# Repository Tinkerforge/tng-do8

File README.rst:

TNG DO8
=======

**This TNG module is currently in development.**

This repository contains the firmware source code and the hardware design
files. The documentation generator configs can be found at
https://github.com/Tinkerforge/generators

Repository Content
------------------

software/:
 * examples/: Examples for all supported languages
 * build/: Compiled files
 * src/: Source code of firmware
 * Makefile: Makefile to build project

hardware/:
 * Contains KiCad project files and additionally schematics as PDF

datasheets/:
 * Contains datasheets for sensors and complex ICs that are used

Hardware
--------

The hardware is designed with the open source EDA Suite KiCad
(http://www.kicad.org). Before you are able to open the files,
you have to install the Tinkerforge kicad-libraries
(https://github.com/Tinkerforge/kicad-libraries). You can either clone
them directly in hardware/ or clone them in a separate folder and
symlink them into hardware/
(ln -s kicad_path/kicad-libraries project_path/hardware). After that you
can open the .pro file in hardware/ with KiCad and from there view and
modify the schematics and the PCB layout.

Software
--------

If you want to do your own Brick/Bricklet firmware development we highly
recommend that you use our build environment setup script and read the
tutorial (https://www.tinkerforge.com/en/doc/Tutorials/Tutorial_Build_Environment/Tutorial.html).

To compile the C code we recommend you to install the newest GNU Arm Embedded
Toolchain (https://launchpad.net/gcc-arm-embedded/+download).
You also need to install bricklib2 (https://github.com/Tinkerforge/bricklib2).

You can either clone it directly in software/src/ or clone it in a
separate folder and symlink it into software/src/
(ln -s bricklib_path/bricklib2 project_path/software/src/). Finally make sure to
have CMake installed (http://www.cmake.org/cmake/resources/software.html).

After that you can build the firmware by invoking make in software/.
The firmware (.zbin) can then be found in software/build/ and uploaded
with brickv (click button "Flashing" on start screen).

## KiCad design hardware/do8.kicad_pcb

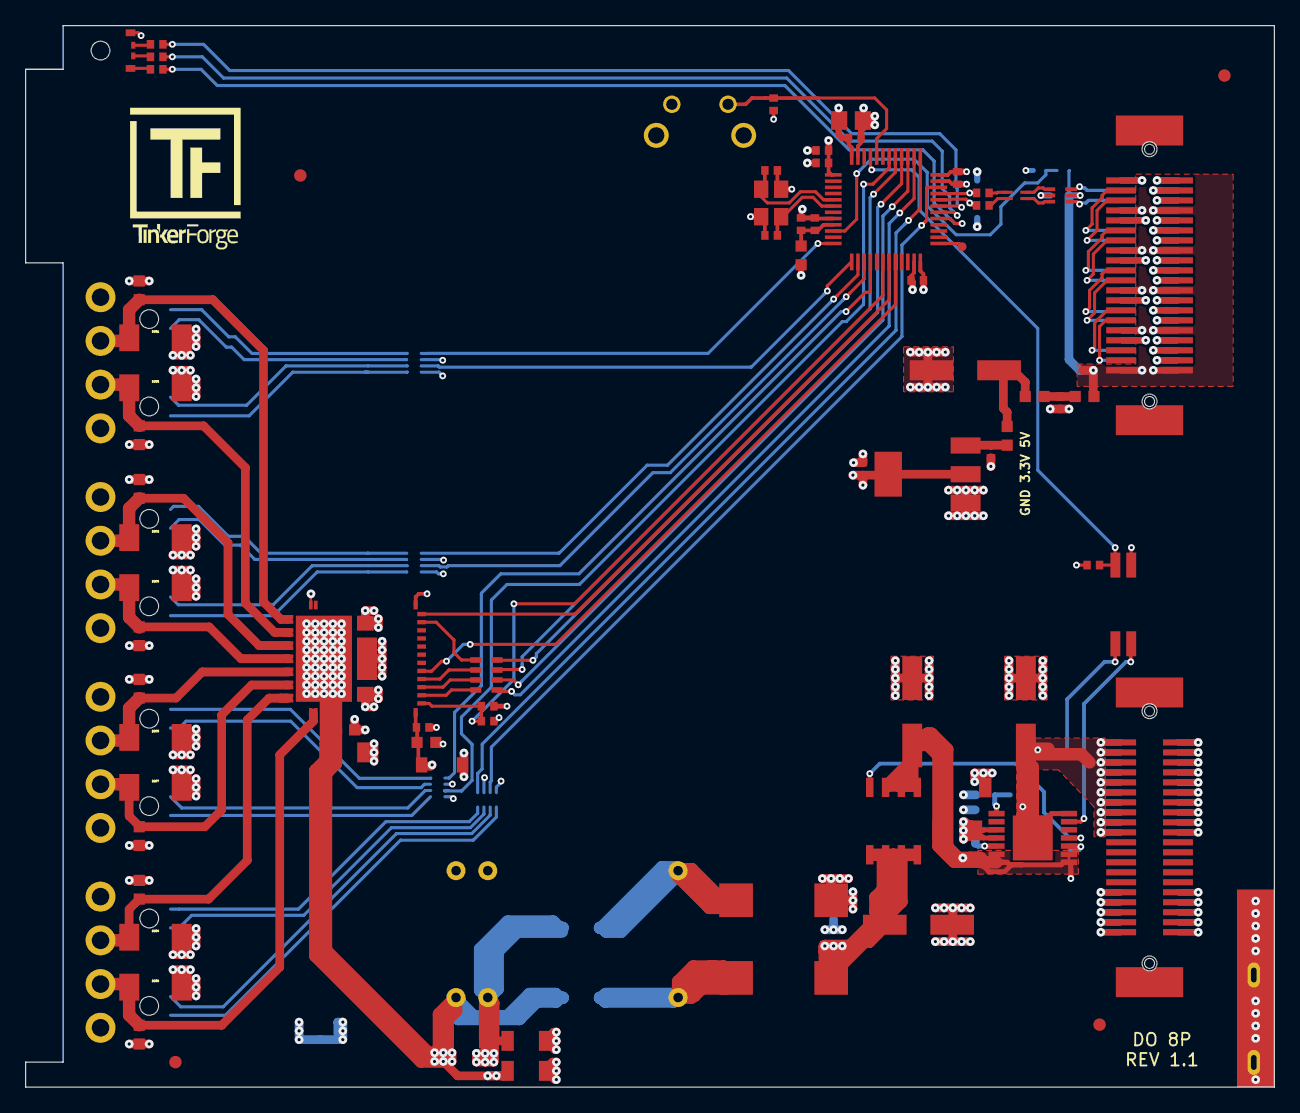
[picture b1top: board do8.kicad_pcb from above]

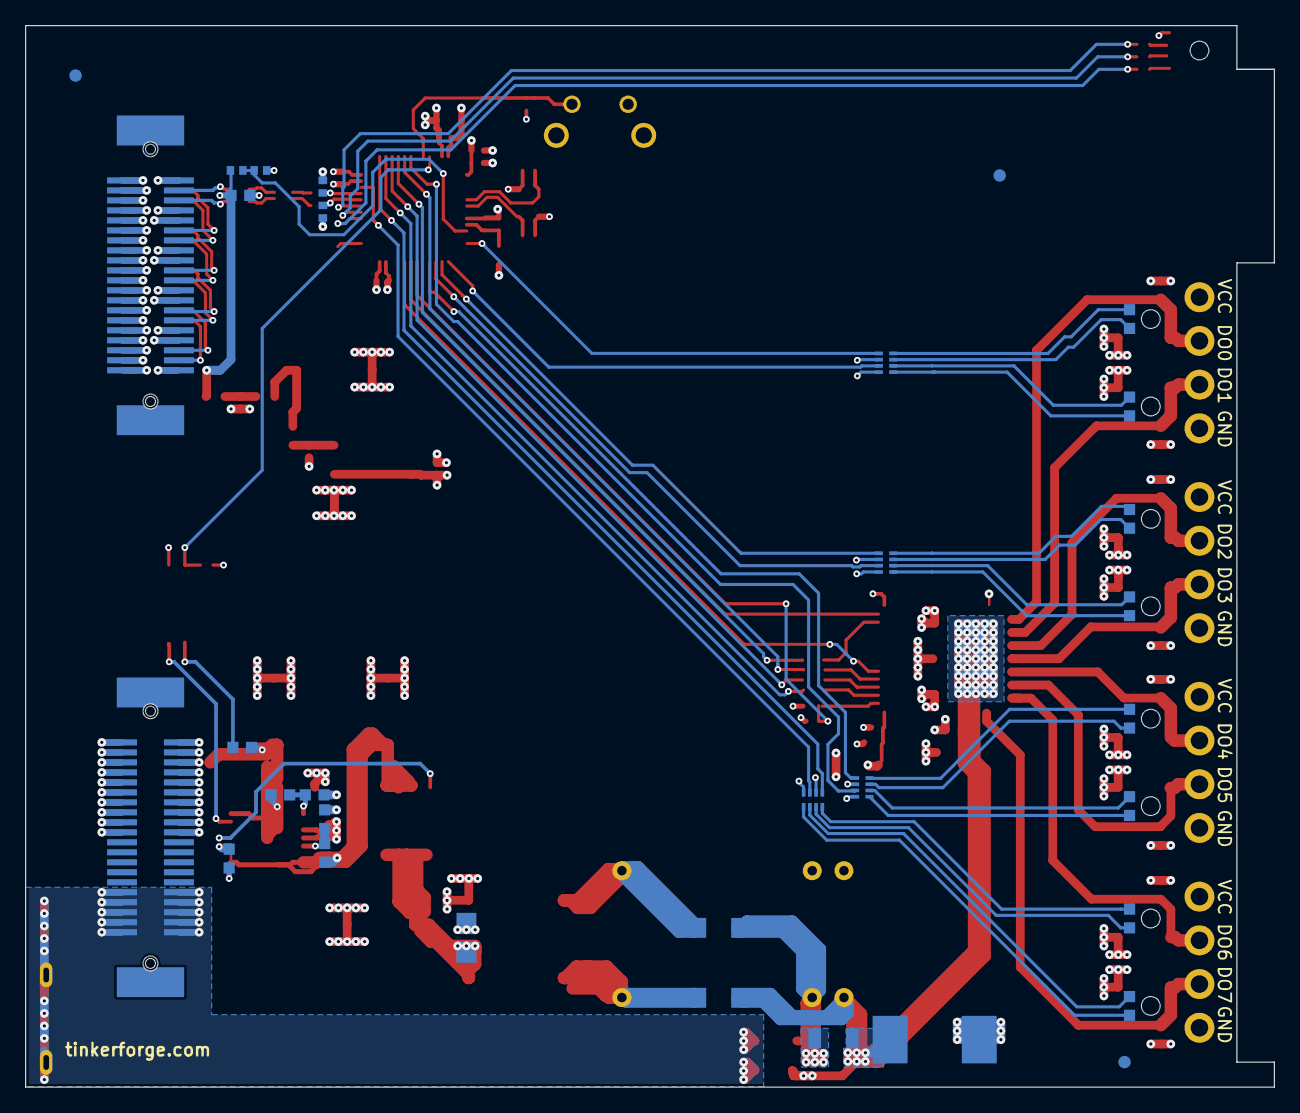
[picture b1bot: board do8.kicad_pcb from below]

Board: 4 copper layers, 100.0 x 85.0 mm, 115 parts (33 on the bottom side), 93 nets.

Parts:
C101, C102, C116, C117: 1uF; C0402F
C103, C104, C105, C106, C107, C112, C212: 100nF; C0402F
C108, C109: 33pF; C0402F
C110: 10uF; C0805E
C111: 100uF; ELKO_63
C113, C114: 47pF; C0402F
C115, C213: 2.2uF; C0603F
C118, C121: 10uF/50V; C1206
C119, C120: 0; C1206
C122, C123, C124: 100uF/35V; ELKO_63
C125, C126: 10uF/35V; C1206
C127, C128: 1nF/2kV; C1206
C202, C203, C204, C205, C206, C207, C209, C211: 22n/50V; C0603F
C208: 4.7uF/50V; C1206
C210: 100nF/50V; C0603F
C214: 15pF; C0402F
D101: 3.0SMI30CATR; SMC
D201, D202, D203, D204, D205, D206, D207, D208: SMBJ24CA; SMB
D209: SMF3.3; SOD-123FL
D210, D211, D212, D213, D214, D215, D216, D217: LED; LED-LP
Fiducial_Mark: VAL**; Fiducial_Mark
Fiducial_Mark#2, Fiducial_Mark#3, Fiducial_Mark#4, Fiducial_Mark#5, Fiducial_Mark#6, Fiducial_Mark#7: VAL**; Fiducial_Mark
J101: TNG-Power-TOP; TNG-40-TOP
J102: TNG-Power-BTM; TNG-40-BTM
J103: TNG-Data-TOP; TNG-40-TOP
J104: TNG-Data-BTM; TNG-40-BTM
L101: FB; R0603F
L102, L103, L104: INDUCTs; R0603F
L105: 744230900; WE-CNSW-0603
LED101: EASV3015RGBA0; LED-RGB-LP
P102: Debug; DEBUG_PAD
P103: PE; PE_Hook
P201: OUTPUT0; OQ_4P
P202: OUTPUT1; OQ_4P
P203: OUTPUT2; OQ_4P
P204: OUTPUT3; OQ_4P
Q101: FDS8449; SOIC-8-MOSFET
R101, R107, R108: 1k; R0402F
R102, R105: 0; R0402F
R103, R104: 22; R0402F
R106: 56; R0402F
R109: 10k; R0402F
R110, R115: 10k; R0603F
R111, R112: DNP; R0603F
R113: 22; R0603F
R114: 68k; R0603F
R116: VC1206K201R030; R1206
R201: 47k; R0402F
RP201: 180; 4X0603
RP202, RP203, RP204, RP205: 470; 4X0402
SW101: BOOT; TACT-6MM-HOR
T101: 744273222; WE-SL5
U101: STM32F070CBT6; LQFP48
U102: AZ1117EH; SOT-223
U103: 82400152; SOT563-SPEC
U104: DNP; TEL10
U105: TLP293; SOP4
U106: STEF01; HTSSOP14
U201: ISO8200AQ; TFQFPN32
X101: 8MHz; CRYSTAL_3225

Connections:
3V3: C101.1, C103.1, C104.1, C105.1, C106.1, C110.1, C116.1, C212.2, C213.2, D209.2, L101.1, LED101.1, R109.2, RP202.2, RP202.4, RP203.2, RP203.4, RP204.2, RP204.4, RP205.2, RP205.4, SW101.1, U101.1, U101.24, U101.36, U101.48, U102.2, U201.20
5VA: C115.1, J103.7, J103.8, J103.15, J103.16, J103.23, J103.24, J103.31, J103.32, J103.39, J103.40, J104.7, J104.8, J104.15, J104.16, J104.23, J104.24, J104.31, J104.32, J104.39, J104.40, L104.1, R107.1, U103.5
+5V: C111.1, L102.1, L103.2
AGND: C118.2, C120.1, C128.2, C202.1, C203.1, C204.1, C205.1, C206.1, C207.1, C208.1, C209.1, C210.1, C211.1, D101.2, D201.1, D202.1, D203.1, D204.1, D205.1, D206.1, D207.1, D208.1, P201.4, P202.4, P203.4, P204.4, R116.2, U104.10, U201.3, U201.TGND
AGNDA: C121.2, C122.2, C123.2, C124.2, C125.2, C126.2, J101.2, J101.4, J101.6, J101.8, J101.10, J101.12, J101.14, J101.16, J101.18, J101.20, J102.1, J102.3, J102.5, J102.7, J102.9, J102.11, J102.13, J102.15, J102.17, J102.19, R112.2, R115.2, T101.2, U106.3, U106.4
AIN0: R107.2, R108.1, U101.10
Earth: C127.2, C128.1, J101.31, J101.32, J101.33, J101.34, J101.35, J101.36, J101.37, J101.38, J101.39, J101.40, J102.31, J102.32, J102.33, J102.34, J102.35, J102.36, J102.37, J102.38, J102.39, J102.40, P103.1
GND: C101.2, C102.2, C103.2, C104.2, C105.2, C106.2, C107.2, C108.1, C109.1, C110.2, C111.2, C112.2, C113.2, C114.2, C115.2, C116.2, C117.2, C212.1, C213.1, C214.1, D209.1, J103.1, J103.2, J103.4, J103.6, J103.9, J103.10, J103.12, J103.14, J103.17, J103.18, J103.20, J103.22, J103.25, J103.26, J103.28, J103.30, J103.33, J103.34, J103.36, J103.38, J104.1, J104.2, J104.3, J104.5, J104.9, J104.10, J104.11, J104.13, J104.17, J104.18, J104.19, J104.21, J104.25, J104.26, J104.27, J104.29, J104.33, J104.34, J104.35, J104.37, R101.1, R108.2, R201.2, U101.8, U101.23, U101.35, U101.47, U102.1, U103.2, U105.3, U201.1, X101.3
LED0: RP202.1, U101.12
LED1: RP202.3, U101.13
LED2: RP203.1, U101.14
LED3: RP203.3, U101.15
LED4: RP204.1, U101.16
LED5: RP204.3, U101.42
LED6: RP205.1, U101.37
LED7: RP205.3, U101.34
LEDB: R106.1, U101.31
LEDG: R105.1, U101.30
LEDR: R102.1, U101.29
unnamed: C102.1, C107.1, L101.2, U101.9
unnamed: C108.2, U101.5, X101.2
unnamed: C109.2, U101.6, X101.1
unnamed: C112.1, L103.1, L104.2
unnamed: C117.1, L102.2, U102.3
unnamed: C119.2, T101.4, U104.16
unnamed: C120.2, T101.3, U104.1
unnamed: C121.1, C123.1, Q101.D, T101.1
unnamed: C202.2, D208.2, P204.3, U201.18, U201.19
unnamed: C203.2, D204.2, P204.2, U201.16, U201.17
unnamed: C204.2, D207.2, P203.3, U201.14, U201.15
unnamed: C205.2, D203.2, P203.2, U201.12, U201.13
unnamed: C206.2, D206.2, P202.3, U201.10, U201.11
unnamed: C207.2, D202.2, P202.2, U201.8, U201.9
unnamed: C209.2, D205.2, P201.3, U201.6, U201.7
unnamed: C211.2, D201.2, P201.2, U201.4, U201.5
unnamed: D210.1, RP202.7
unnamed: D210.2, RP202.8
unnamed: D211.1, RP202.5
unnamed: D211.2, RP202.6
unnamed: D212.1, RP203.7
unnamed: D212.2, RP203.8
unnamed: D213.1, RP203.5
unnamed: D213.2, RP203.6
unnamed: D214.1, RP204.7
unnamed: D214.2, RP204.8
unnamed: D215.1, RP204.5
unnamed: D215.2, RP204.6
unnamed: D216.1, RP205.7
unnamed: D216.2, RP205.8
unnamed: D217.1, RP205.5
unnamed: D217.2, RP205.6
unnamed: J103.3, J104.12
unnamed: J103.5, J104.14
unnamed: J103.11, J104.20
unnamed: J103.13, J104.22
unnamed: J103.19, J104.28
unnamed: J103.21, J104.30
unnamed: J103.27, J104.36
unnamed: J103.29, J104.38
unnamed: LED101.2, R106.2
unnamed: LED101.3, R105.2
unnamed: LED101.4, R102.2
unnamed: P102.1, U101.25
unnamed: Q101.G, U106.11
unnamed: R101.2, SW101.2, U101.44
unnamed: R110.2, U105.1
unnamed: R111.2, R112.1, U106.5
unnamed: R113.2, U106.10
unnamed: R114.2, R115.1, U106.1
unnamed: RP201.1, U201.22
unnamed: RP201.2, U201.23
unnamed: RP201.3, U201.24
unnamed: RP201.4, U201.31
OUT_EN: C214.2, R201.1, U101.18, U201.21
PWR_GOOD: R109.1, U101.45, U105.4
PWR_PG: U105.2, U106.13
SDI: RP201.6, U101.41
SDO: RP201.5, U101.40
USB-DM: C114.1, R104.2, U101.32
USB-DMA: J104.6, U103.4
USB-DMB: L105.1, U103.3
USB-DMC: L105.2, R104.1
USB-DP: C113.1, R103.2, U101.33
USB-DPA: J104.4, U103.6
USB-DPB: L105.4, U103.1
USB-DPC: L105.3, R103.1
VCC: C118.1, C119.1, C127.1, C208.2, C210.2, D101.1, P201.1, P202.1, P203.1, P204.1, R116.1, U104.9, U201.TVCC
VCCPWRA: C122.1, C126.1, J101.1, J101.3, J101.5, J101.7, J101.9, J101.11, J101.13, J101.15, J101.17, J101.19, J102.2, J102.4, J102.6, J102.8, J102.10, J102.12, J102.14, J102.16, J102.18, J102.20, R110.1, R114.1, U106.14, U106.EXP
VO: C124.1, C125.1, Q101.S, R111.1, R113.1, U106.6, U106.7, U106.8, U106.9
~CLK: RP201.7, U101.39
~FAULT: U101.19, U201.32
~PGOOD: U101.20, U201.25
~SS: RP201.8, U101.38

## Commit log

2019-07-05 Add auto-generated TNG DO8 stub
2019-11-22 do8 nearly finished
2019-11-25 some routing
2019-11-26 completely routed
2019-11-28 outline update
2019-12-10 fix name
2019-12-23 update rgb led drill diameter
2019-12-30 fix inductor footprint
2020-01-02 add stuff
2020-01-14 Add examples.
2020-03-02 fix description
2020-03-02 add hook footprint
2020-03-16 examples: Add missing timestamp parameter
2020-05-14 change value
2020-05-14 specify tbd
2020-05-14 Add stub firmware
2020-06-24 rust: Update example
2020-07-07 fix diodes
2020-07-20 Add ISO8200 driver
2020-07-27 Use HAL Config from bricklib2
2020-07-27 Use fixed hal_pcd.c from bricklib2
2020-07-27 Add TIM defines for status LEDs
2020-08-25 examples: Adapt to API changes
2020-09-04 version 1.1.
    fix footprints
2020-09-07 fix values
2020-09-07 fix footprint
2020-09-08 fix routing
2020-09-08 all footprints updated
2020-09-09 remove galvanic isolation as default
2020-09-10 fix 3d stuff
2021-10-25 Update KiCad link
    https://www.kicad.org/blog/2021/10/Avoid-links-to-former-kicad-domain/

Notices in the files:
hardware/do8.kicad_pcb:
Licensed under CERN OHL v.1.1
Copyright (©) 2020, B.Nordmeyer
Copyright Tinkerforge GmbH 2020.
This documentation describes Open Hardware and is licensed under the
CERN OHL v. 1.1.
